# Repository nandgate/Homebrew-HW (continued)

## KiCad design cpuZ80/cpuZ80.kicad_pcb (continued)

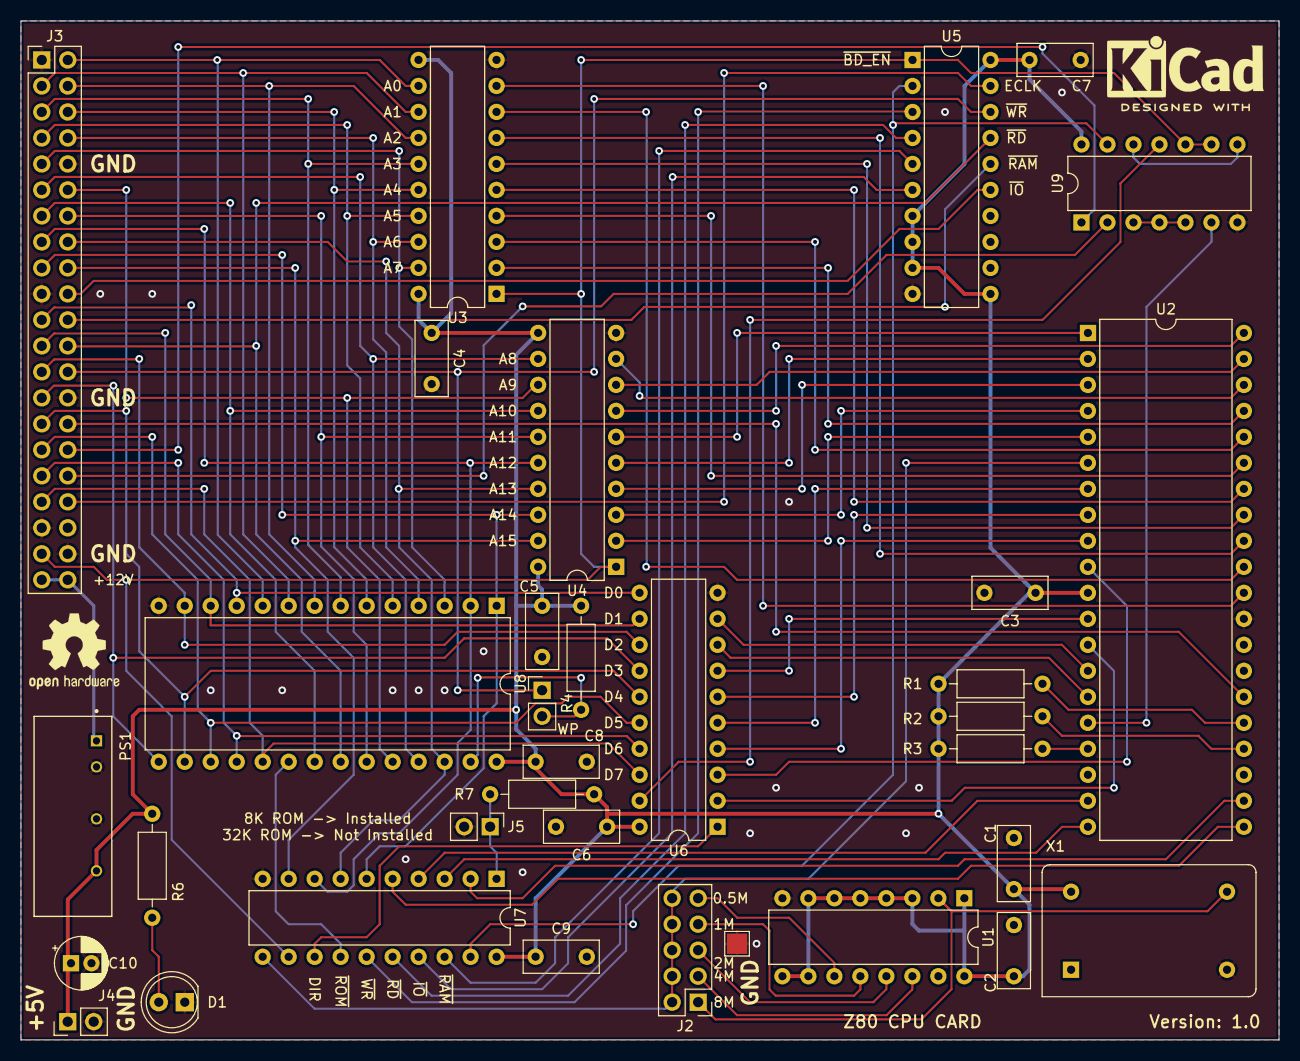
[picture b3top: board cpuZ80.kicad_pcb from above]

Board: 2 copper layers, 122.9 x 99.6 mm, 34 parts (0 on the bottom side), 87 nets.

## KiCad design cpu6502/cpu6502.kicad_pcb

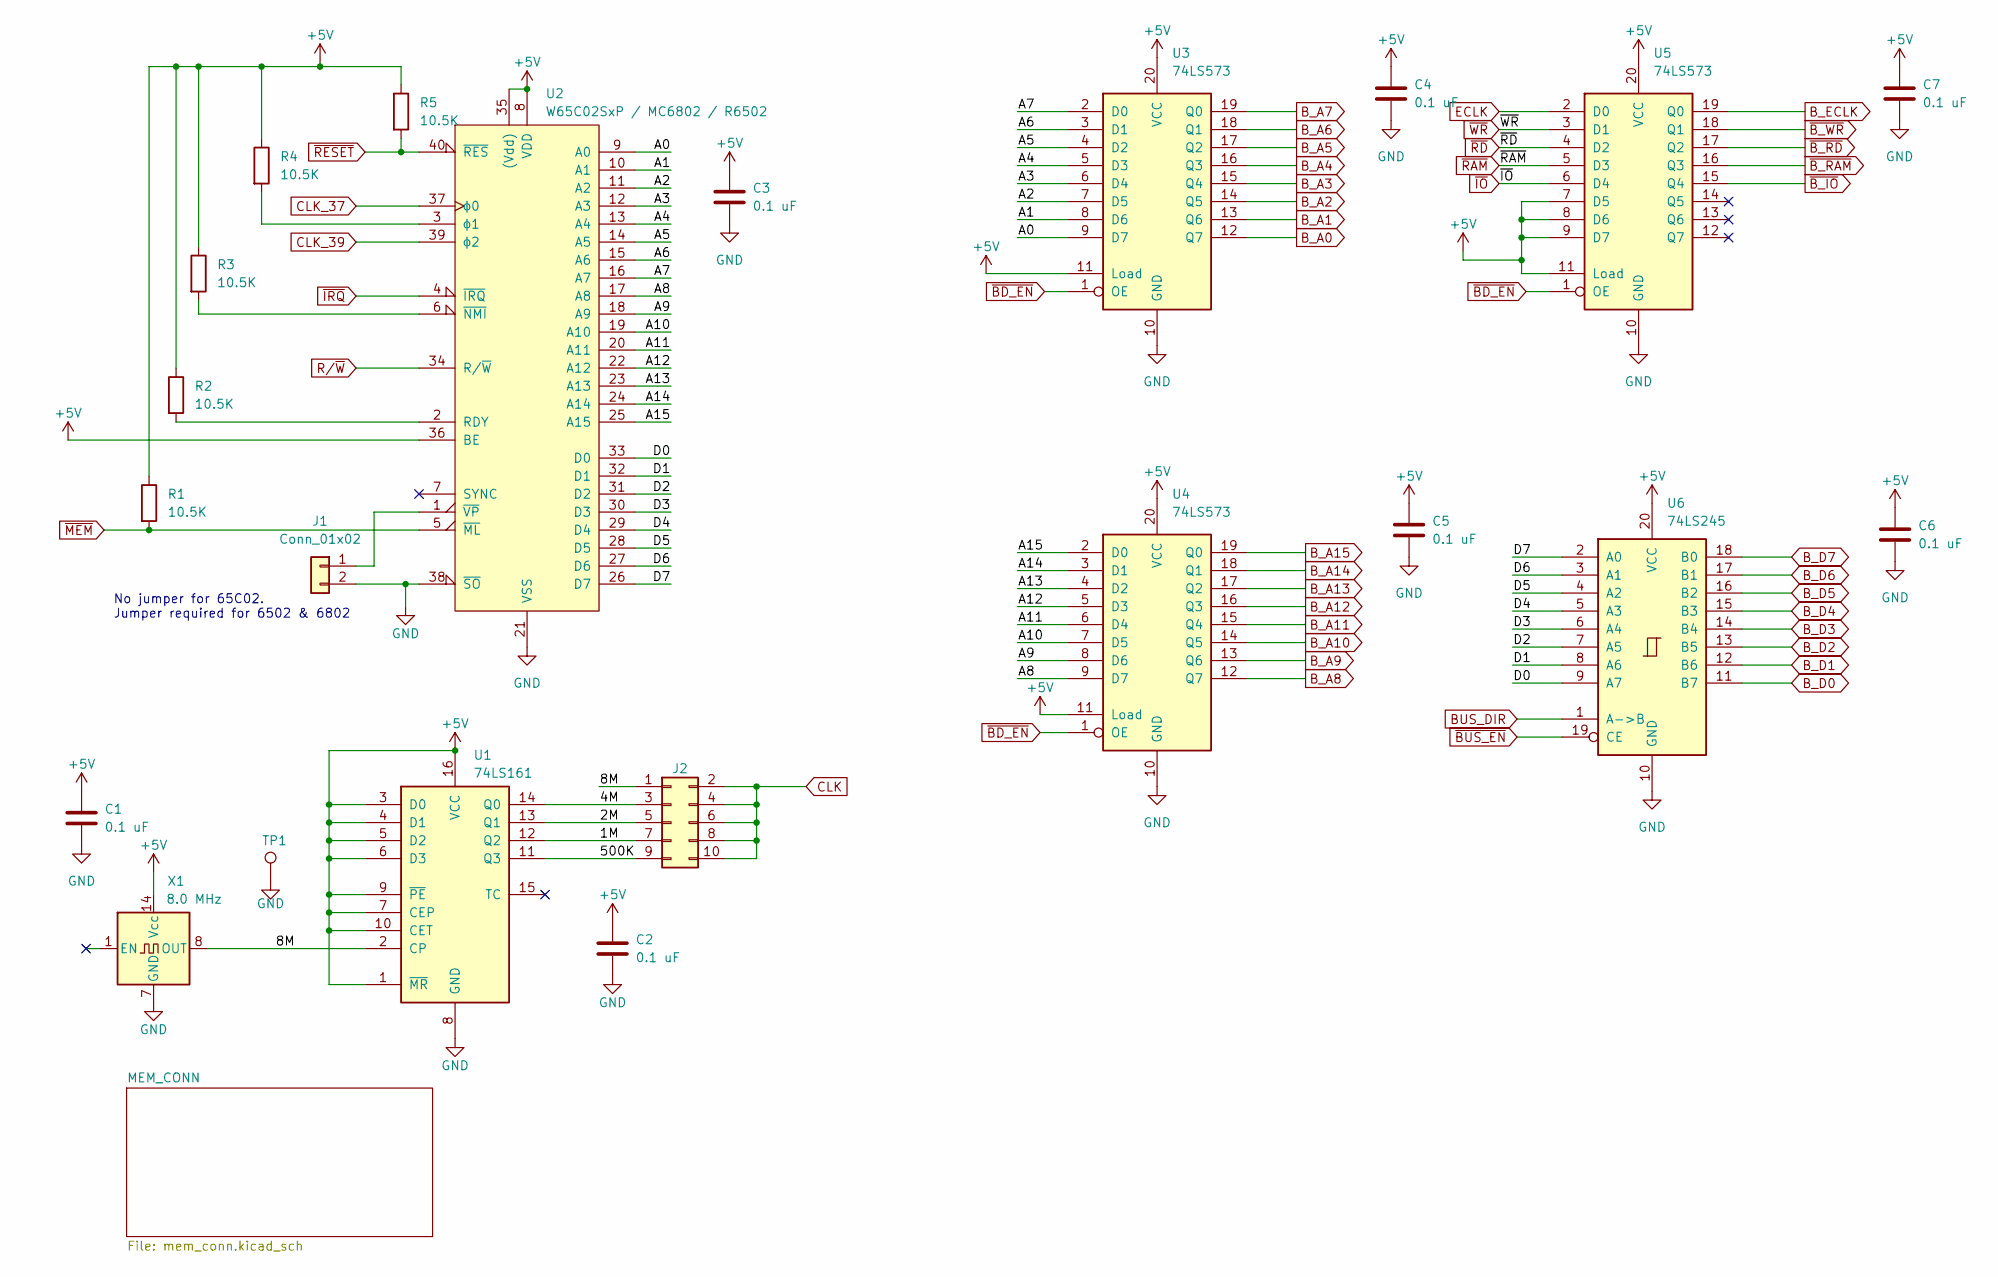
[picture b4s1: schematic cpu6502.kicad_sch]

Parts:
C1, C2, C3, C4, C5, C6, C7: 0.1 uF; C_Rect_L7.2mm_W3.0mm_P5.00mm_FKS2_FKP2_MKS2_MKP2
J1: Conn_01x02; PinHeader_1x02_P2.54mm_Vertical
J2: Conn_02x05_Odd_Even; PinHeader_2x05_P2.54mm_Vertical
R1, R2, R3, R4, R5: 10.5K; R_Axial_DIN0207_L6.3mm_D2.5mm_P10.16mm_Horizontal
TP1: TestPoint; TestPoint_Pad_2.0x2.0mm
U1: 74LS161; DIP-16_W7.62mm
U2: W65C02SxP / MC6802 / R6502; DIP-40_W15.24mm
U3, U4, U5: 74LS573; DIP-20_W7.62mm
U6: 74LS245; DIP-20_W7.62mm
X1: 8.0 MHz; Oscillator_DIP-14

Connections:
+5V: C1.1, C2.1, C3.1, C4.1, C5.1, C6.1, C7.1, R1.1, R2.1, R3.1, R4.1, R5.1, U1.1 (~MR), U1.3 (D0), U1.4 (D1), U1.5 (D2), U1.6 (D3), U1.7 (CEP), U1.9 (~PE), U1.10 (CET), U1.16 (VCC), U2.8 (VDD), U2.35 ((Vdd)), U2.36 (BE), U3.11 (Load), U3.20 (VCC), U4.11 (Load), U4.20 (VCC), U5.7 (D5), U5.8 (D6), U5.9 (D7), U5.11 (Load), U5.20 (VCC), U6.20 (VCC), X1.14 (Vcc); also elsewhere on the board
/1M: J2.7, U1.12 (Q2)
/2M: J2.5, U1.13 (Q1)
/4M: J2.3, U1.14 (Q0)
/8M: J2.1, U1.2 (CP), X1.8 (OUT)
/500K: J2.9, U1.11 (Q3)
/A0: U2.9 (A0), U3.9 (D7)
/A1: U2.10 (A1), U3.8 (D6)
/A2: U2.11 (A2), U3.7 (D5)
/A3: U2.12 (A3), U3.6 (D4)
/A4: U2.13 (A4), U3.5 (D3)
/A5: U2.14 (A5), U3.4 (D2)
/A6: U2.15 (A6), U3.3 (D1)
/A7: U2.16 (A7), U3.2 (D0)
/A8: U2.17 (A8), U4.9 (D7)
/A9: U2.18 (A9), U4.8 (D6)
/A10: U2.19 (A10), U4.7 (D5)
/A11: U2.20 (A11), U4.6 (D4)
/A12: U2.22 (A12), U4.5 (D3)
/A13: U2.23 (A13), U4.4 (D2)
/A14: U2.24 (A14), U4.3 (D1)
/A15: U2.25 (A15), U4.2 (D0)
/D0: U2.33 (D0), U6.9 (A7)
/D1: U2.32 (D1), U6.8 (A6)
/D2: U2.31 (D2), U6.7 (A5)
/D3: U2.30 (D3), U6.6 (A4)
/D4: U2.29 (D4), U6.5 (A3)
/D5: U2.28 (D5), U6.4 (A2)
/D6: U2.27 (D6), U6.3 (A1)
/D7: U2.26 (D7), U6.2 (A0)
BUS_DIR: U6.1 (A->B); also elsewhere on the board
B_A0: U3.12 (Q7); also elsewhere on the board
B_A1: U3.13 (Q6); also elsewhere on the board
B_A2: U3.14 (Q5); also elsewhere on the board
B_A3: U3.15 (Q4); also elsewhere on the board
B_A4: U3.16 (Q3); also elsewhere on the board
B_A5: U3.17 (Q2); also elsewhere on the board
B_A6: U3.18 (Q1); also elsewhere on the board
B_A7: U3.19 (Q0); also elsewhere on the board
B_A8: U4.12 (Q7); also elsewhere on the board
B_A9: U4.13 (Q6); also elsewhere on the board
B_A10: U4.14 (Q5); also elsewhere on the board
B_A11: U4.15 (Q4); also elsewhere on the board
B_A12: U4.16 (Q3); also elsewhere on the board
B_A13: U4.17 (Q2); also elsewhere on the board
B_A14: U4.18 (Q1); also elsewhere on the board
B_A15: U4.19 (Q0); also elsewhere on the board
B_D0: U6.11 (B7); also elsewhere on the board
B_D1: U6.12 (B6); also elsewhere on the board
B_D2: U6.13 (B5); also elsewhere on the board
B_D3: U6.14 (B4); also elsewhere on the board
B_D4: U6.15 (B3); also elsewhere on the board
B_D5: U6.16 (B2); also elsewhere on the board
B_D6: U6.17 (B1); also elsewhere on the board
B_D7: U6.18 (B0); also elsewhere on the board
B_ECLK: U5.19 (Q0); also elsewhere on the board
CLK: J2.2, J2.4, J2.6, J2.8, J2.10; also elsewhere on the board
CLK_37: U2.37 (ϕ0); also elsewhere on the board
CLK_39: U2.39 (ϕ2); also elsewhere on the board
ECLK: U5.2 (D0); also elsewhere on the board
GND: C1.2, C2.2, C3.2, C4.2, C5.2, C6.2, C7.2, J1.2, TP1.1, U1.8 (GND), U2.21 (VSS), U2.38 (~SO), U3.10 (GND), U4.10 (GND), U5.10 (GND), U6.10 (GND), X1.7 (GND); also elsewhere on the board
unnamed: J1.1, U2.1 (~VP)
unnamed: R2.2, U2.2 (RDY)
unnamed: R3.2, U2.6 (~NMI)
unnamed: R4.2, U2.3 (ϕ1)
R/~W: U2.34 (R/~W); also elsewhere on the board
~BD_EN: U3.1 (OE), U4.1 (OE), U5.1 (OE); also elsewhere on the board
~BUS_EN: U6.19 (CE); also elsewhere on the board
~B_IO: U5.15 (Q4); also elsewhere on the board
~B_RAM: U5.16 (Q3); also elsewhere on the board
~B_RD: U5.17 (Q2); also elsewhere on the board
~B_WR: U5.18 (Q1); also elsewhere on the board
~IO: U5.6 (D4); also elsewhere on the board
~IRQ: U2.4 (~IRQ); also elsewhere on the board
~MEM: R1.2, U2.5 (~ML); also elsewhere on the board
~RAM: U5.5 (D3); also elsewhere on the board
~RD: U5.4 (D2); also elsewhere on the board
~RESET: R5.2, U2.40 (~RES); also elsewhere on the board
~WR: U5.3 (D1); also elsewhere on the board

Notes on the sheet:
No jumper for 65C02. Jumper required for 6502 & 6802

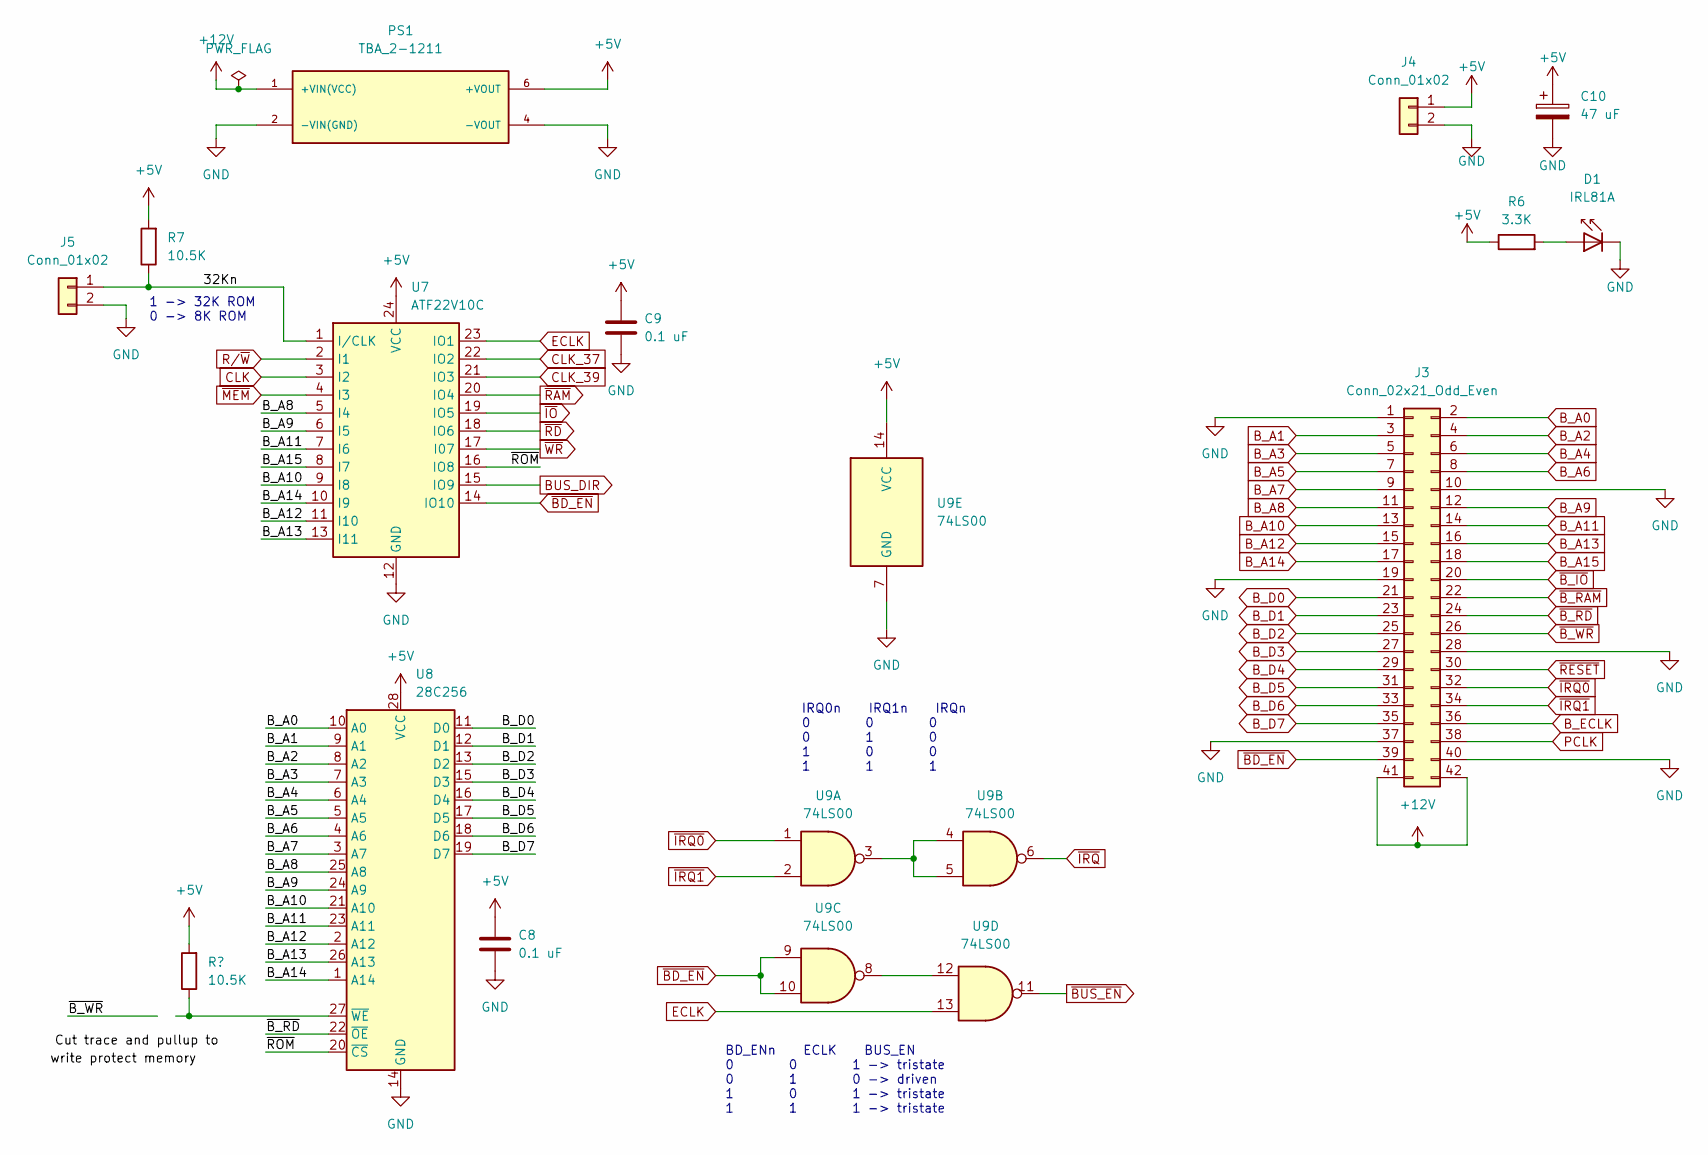
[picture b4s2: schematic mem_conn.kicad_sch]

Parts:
C8, C9: 0.1 uF; C_Rect_L7.2mm_W3.0mm_P5.00mm_FKS2_FKP2_MKS2_MKP2
C10: 47 uF; CP_Radial_D5.0mm_P2.00mm
D1: IRL81A; LED_D5.0mm
J3: Conn_02x21_Odd_Even; PinHeader_2x21_P2.54mm_Vertical
J4, J5: Conn_01x02; PinHeader_1x02_P2.54mm_Vertical
PS1: TBA_2-1211; CONV_TBA_2-1211; PARTREV April 19, 2021
R6: 3.3K; R_Axial_DIN0207_L6.3mm_D2.5mm_P10.16mm_Horizontal
R7: 10.5K; R_Axial_DIN0207_L6.3mm_D2.5mm_P10.16mm_Horizontal
U7: ATF22V10C; DIP-24_W7.62mm
U8: 28C256; DIP-28_W15.24mm
U9: 74LS00; DIP-14_W7.62mm

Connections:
+5V: C8.1, C9.1, C10.1, J4.1, PS1.6 (+VOUT), R6.1, R7.2, U7.24 (VCC), U8.28 (VCC), U9.14 (VCC); also elsewhere on the board
+12V: J3.41, J3.42, PS1.1 (+VIN(VCC))
/MEM_CONN/32Kn: J5.1, R7.1, U7.1 (I/CLK)
/MEM_CONN/~ROM: U7.16 (IO8), U8.20 (~CS)
BUS_DIR: U7.15 (IO9); also elsewhere on the board
B_A0: J3.2, U8.10 (A0); also elsewhere on the board
B_A1: J3.3, U8.9 (A1); also elsewhere on the board
B_A2: J3.4, U8.8 (A2); also elsewhere on the board
B_A3: J3.5, U8.7 (A3); also elsewhere on the board
B_A4: J3.6, U8.6 (A4); also elsewhere on the board
B_A5: J3.7, U8.5 (A5); also elsewhere on the board
B_A6: J3.8, U8.4 (A6); also elsewhere on the board
B_A7: J3.9, U8.3 (A7); also elsewhere on the board
B_A8: J3.11, U7.5 (I4), U8.25 (A8); also elsewhere on the board
B_A9: J3.12, U7.6 (I5), U8.24 (A9); also elsewhere on the board
B_A10: J3.13, U7.9 (I8), U8.21 (A10); also elsewhere on the board
B_A11: J3.14, U7.7 (I6), U8.23 (A11); also elsewhere on the board
B_A12: J3.15, U7.11 (I10), U8.2 (A12); also elsewhere on the board
B_A13: J3.16, U7.13 (I11), U8.26 (A13); also elsewhere on the board
B_A14: J3.17, U7.10 (I9), U8.1 (A14); also elsewhere on the board
B_A15: J3.18, U7.8 (I7); also elsewhere on the board
B_D0: J3.21, U8.11 (D0); also elsewhere on the board
B_D1: J3.23, U8.12 (D1); also elsewhere on the board
B_D2: J3.25, U8.13 (D2); also elsewhere on the board
B_D3: J3.27, U8.15 (D3); also elsewhere on the board
B_D4: J3.29, U8.16 (D4); also elsewhere on the board
B_D5: J3.31, U8.17 (D5); also elsewhere on the board
B_D6: J3.33, U8.18 (D6); also elsewhere on the board
B_D7: J3.35, U8.19 (D7); also elsewhere on the board
B_ECLK: J3.36; also elsewhere on the board
CLK: U7.3 (I2); also elsewhere on the board
CLK_37: U7.22 (IO2); also elsewhere on the board
CLK_39: U7.21 (IO3); also elsewhere on the board
ECLK: U7.23 (IO1), U9.13; also elsewhere on the board
GND: C8.2, C9.2, C10.2, D1.1 (K), J3.1, J3.10, J3.19, J3.28, J3.37, J3.40, J4.2, J5.2, PS1.2 (-VIN(GND)), PS1.4 (-VOUT), U7.12 (GND), U8.14 (GND), U9.7 (GND); also elsewhere on the board
unnamed: D1.2 (A), R6.2
unnamed: U9.3, U9.4, U9.5
unnamed: U9.8, U9.12
PCLK: J3.38
R/~W: U7.2 (I1); also elsewhere on the board
~BD_EN: J3.39, U7.14 (IO10), U9.9, U9.10; also elsewhere on the board
~BUS_EN: U9.11; also elsewhere on the board
~B_IO: J3.20; also elsewhere on the board
~B_RAM: J3.22; also elsewhere on the board
~B_RD: J3.24, U8.22 (~OE); also elsewhere on the board
~B_WR: J3.26, U8.27 (~WE); also elsewhere on the board
~IO: U7.19 (IO5); also elsewhere on the board
~IRQ0: J3.32, U9.1
~IRQ1: J3.34, U9.2
~IRQ: U9.6; also elsewhere on the board
~MEM: U7.4 (I3); also elsewhere on the board
~RAM: U7.20 (IO4); also elsewhere on the board
~RD: U7.18 (IO6); also elsewhere on the board
~RESET: J3.30; also elsewhere on the board
~WR: U7.17 (I07); also elsewhere on the board

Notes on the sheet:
1 -> 32K ROM 0 -> 8K ROM
IRQ0n IRQ1n IRQn 0 0 0 0 1 0 1 0 0 1 1 1
BD_ENn ECLK BUS_EN 0 0 1 -> tristate 0 1 0 -> driven 1 0 1 -> tristate 1 1 1 -> tristate

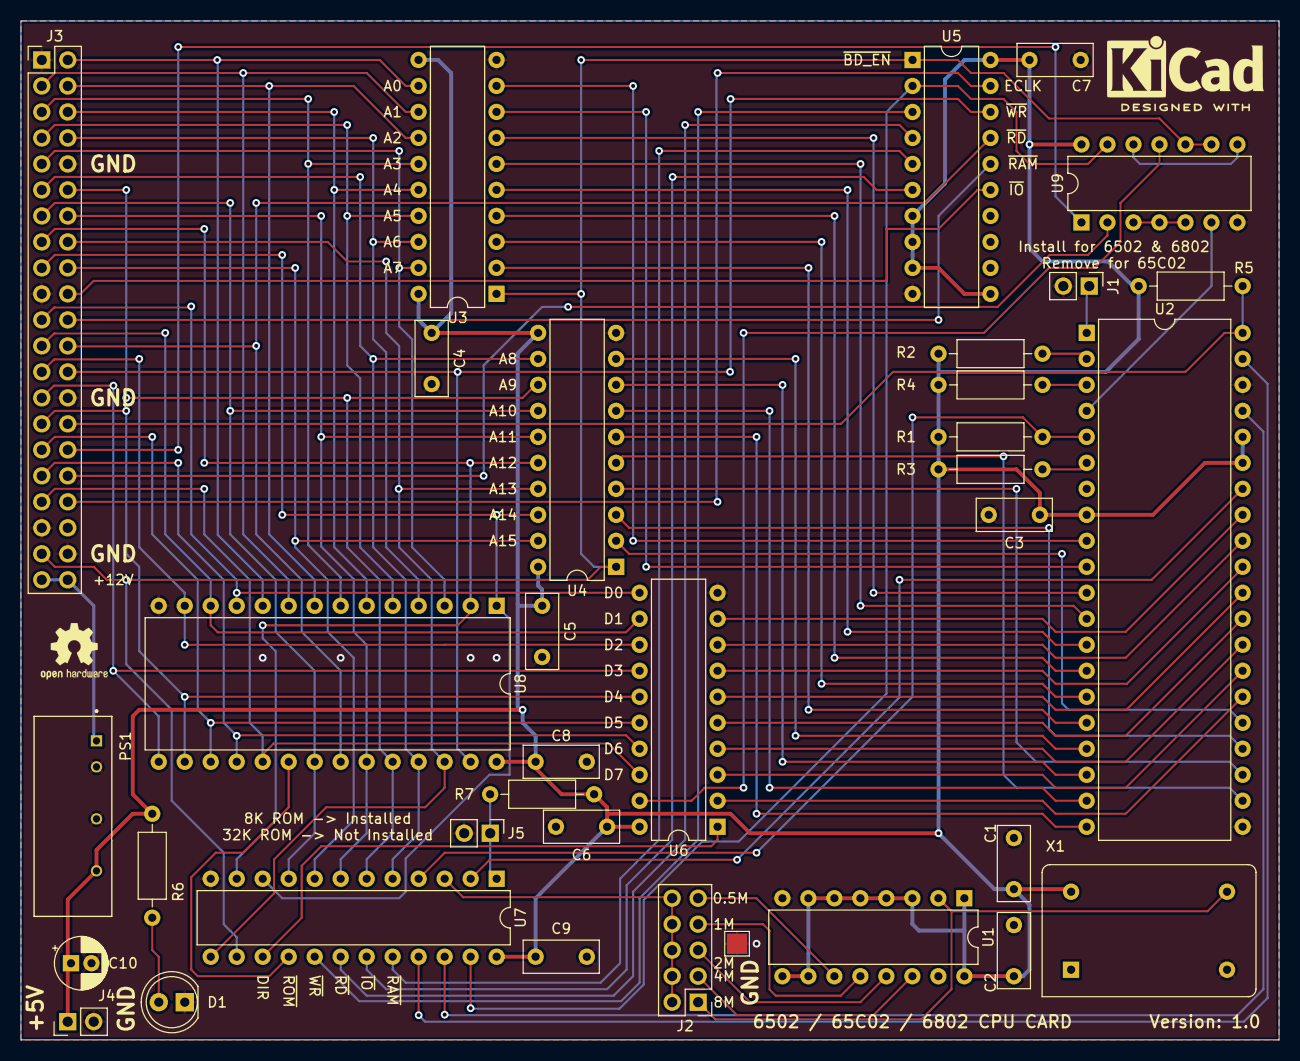
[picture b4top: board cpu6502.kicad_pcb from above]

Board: 2 copper layers, 122.9 x 99.6 mm, 35 parts (0 on the bottom side), 87 nets.

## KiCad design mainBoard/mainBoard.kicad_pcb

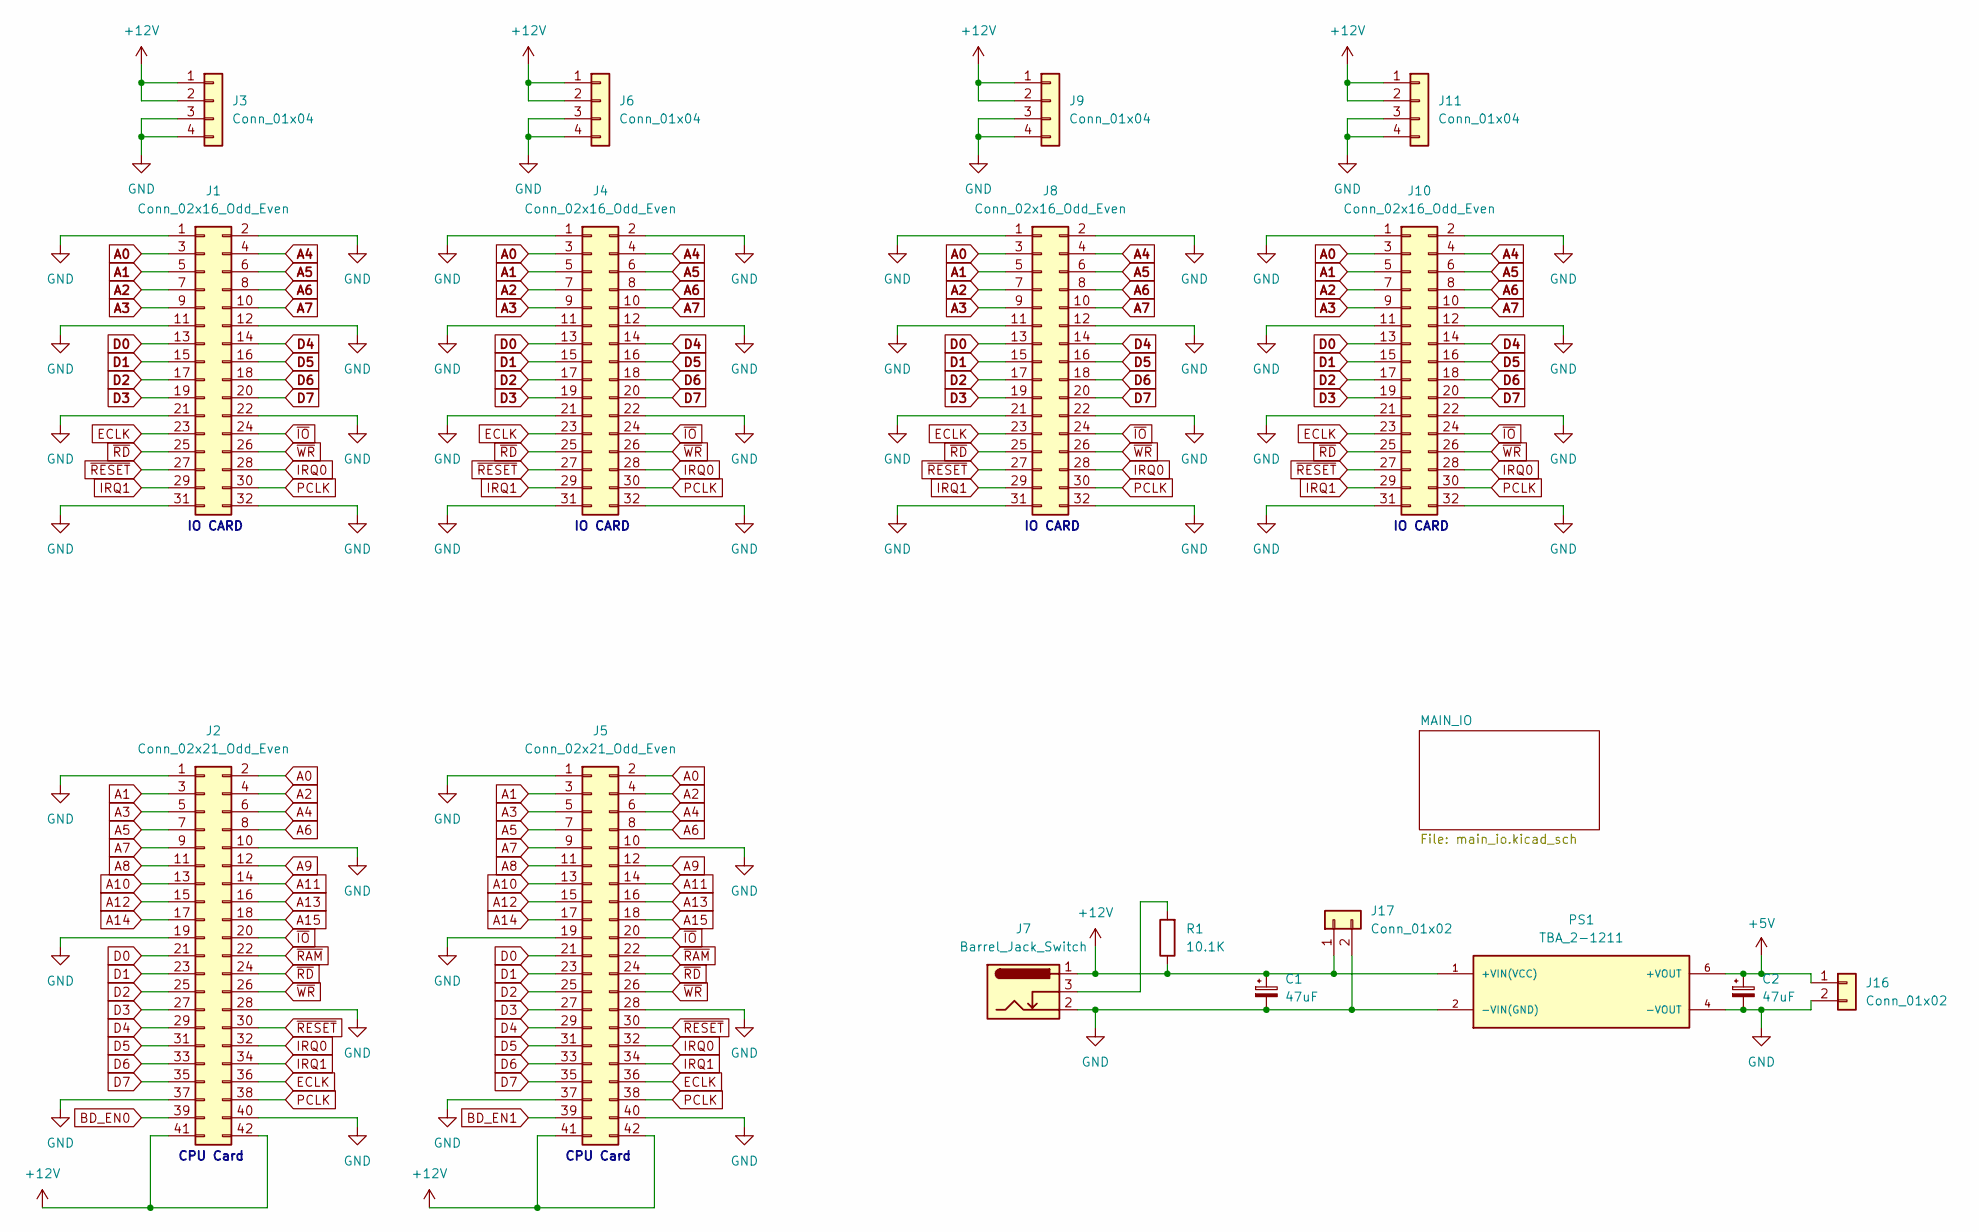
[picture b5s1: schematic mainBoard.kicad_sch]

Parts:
C1, C2: 47uF; CP_Radial_D5.0mm_P2.00mm
J1, J4, J8, J10: Conn_02x16_Odd_Even; PinSocket_2x16_P2.54mm_Vertical
J2, J5: Conn_02x21_Odd_Even; PinSocket_2x21_P2.54mm_Vertical
J3, J6, J9, J11: Conn_01x04; PinSocket_1x04_P2.54mm_Vertical
J7: Barrel_Jack_Switch; BarrelJack_Wuerth_6941xx301002
J16, J17: Conn_01x02; PinHeader_1x02_P2.54mm_Vertical
PS1: TBA_2-1211; CONV_TBA_2-1211; PARTREV April 19, 2021
R1: 10.1K; R_Axial_DIN0207_L6.3mm_D2.5mm_P10.16mm_Horizontal

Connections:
+5V: C2.1, J16.1, PS1.6 (+VOUT); also elsewhere on the board
+12V: C1.1, J2.41, J2.42, J3.1, J3.2, J5.41, J5.42, J6.1, J6.2, J7.1, J9.1, J9.2, J11.1, J11.2, J17.1, PS1.1 (+VIN(VCC)), R1.1
A0: J1.3, J2.2, J4.3, J5.2, J8.3, J10.3; also elsewhere on the board
A1: J1.5, J2.3, J4.5, J5.3, J8.5, J10.5; also elsewhere on the board
A2: J1.7, J2.4, J4.7, J5.4, J8.7, J10.7; also elsewhere on the board
A3: J1.9, J2.5, J4.9, J5.5, J8.9, J10.9; also elsewhere on the board
A4: J1.4, J2.6, J4.4, J5.6, J8.4, J10.4; also elsewhere on the board
A5: J1.6, J2.7, J4.6, J5.7, J8.6, J10.6; also elsewhere on the board
A6: J1.8, J2.8, J4.8, J5.8, J8.8, J10.8; also elsewhere on the board
A7: J1.10, J2.9, J4.10, J5.9, J8.10, J10.10; also elsewhere on the board
A8: J2.11, J5.11; also elsewhere on the board
A9: J2.12, J5.12; also elsewhere on the board
A10: J2.13, J5.13; also elsewhere on the board
A11: J2.14, J5.14; also elsewhere on the board
A12: J2.15, J5.15; also elsewhere on the board
A13: J2.16, J5.16; also elsewhere on the board
A14: J2.17, J5.17; also elsewhere on the board
A15: J2.18, J5.18; also elsewhere on the board
BD_EN0: J2.39; also elsewhere on the board
BD_EN1: J5.39; also elsewhere on the board
D0: J1.13, J2.21, J4.13, J5.21, J8.13, J10.13; also elsewhere on the board
D1: J1.15, J2.23, J4.15, J5.23, J8.15, J10.15; also elsewhere on the board
D2: J1.17, J2.25, J4.17, J5.25, J8.17, J10.17; also elsewhere on the board
D3: J1.19, J2.27, J4.19, J5.27, J8.19, J10.19; also elsewhere on the board
D4: J1.14, J2.29, J4.14, J5.29, J8.14, J10.14; also elsewhere on the board
D5: J1.16, J2.31, J4.16, J5.31, J8.16, J10.16; also elsewhere on the board
D6: J1.18, J2.33, J4.18, J5.33, J8.18, J10.18; also elsewhere on the board
D7: J1.20, J2.35, J4.20, J5.35, J8.20, J10.20; also elsewhere on the board
ECLK: J1.23, J2.36, J4.23, J5.36, J8.23, J10.23; also elsewhere on the board
GND: C1.2, C2.2, J1.1, J1.2, J1.11, J1.12, J1.21, J1.22, J1.31, J1.32, J2.1, J2.10, J2.19, J2.28, J2.37, J2.40, J3.3, J3.4, J4.1, J4.2, J4.11, J4.12, J4.21, J4.22, J4.31, J4.32, J5.1, J5.10, J5.19, J5.28, J5.37, J5.40, J6.3, J6.4, J7.2, J8.1, J8.2, J8.11, J8.12, J8.21, J8.22, J8.31, J8.32, J9.3, J9.4, J10.1, J10.2, J10.11, J10.12, J10.21, J10.22, J10.31, J10.32, J11.3, J11.4, J16.2, J17.2, PS1.2 (-VIN(GND)), PS1.4 (-VOUT); also elsewhere on the board
IRQ0: J1.28, J2.32, J4.28, J5.32, J8.28, J10.28; also elsewhere on the board
IRQ1: J1.29, J2.34, J4.29, J5.34, J8.29, J10.29; also elsewhere on the board
unnamed: J7.3, R1.2
PCLK: J1.30, J2.38, J4.30, J5.38, J8.30, J10.30
~IO: J1.24, J2.20, J4.24, J5.20, J8.24, J10.24; also elsewhere on the board
~RAM: J2.22, J5.22; also elsewhere on the board
~RD: J1.25, J2.24, J4.25, J5.24, J8.25, J10.25; also elsewhere on the board
~RESET: J1.27, J2.30, J4.27, J5.30, J8.27, J10.27; also elsewhere on the board
~WR: J1.26, J2.26, J4.26, J5.26, J8.26, J10.26; also elsewhere on the board

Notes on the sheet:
CPU Card
IO CARD

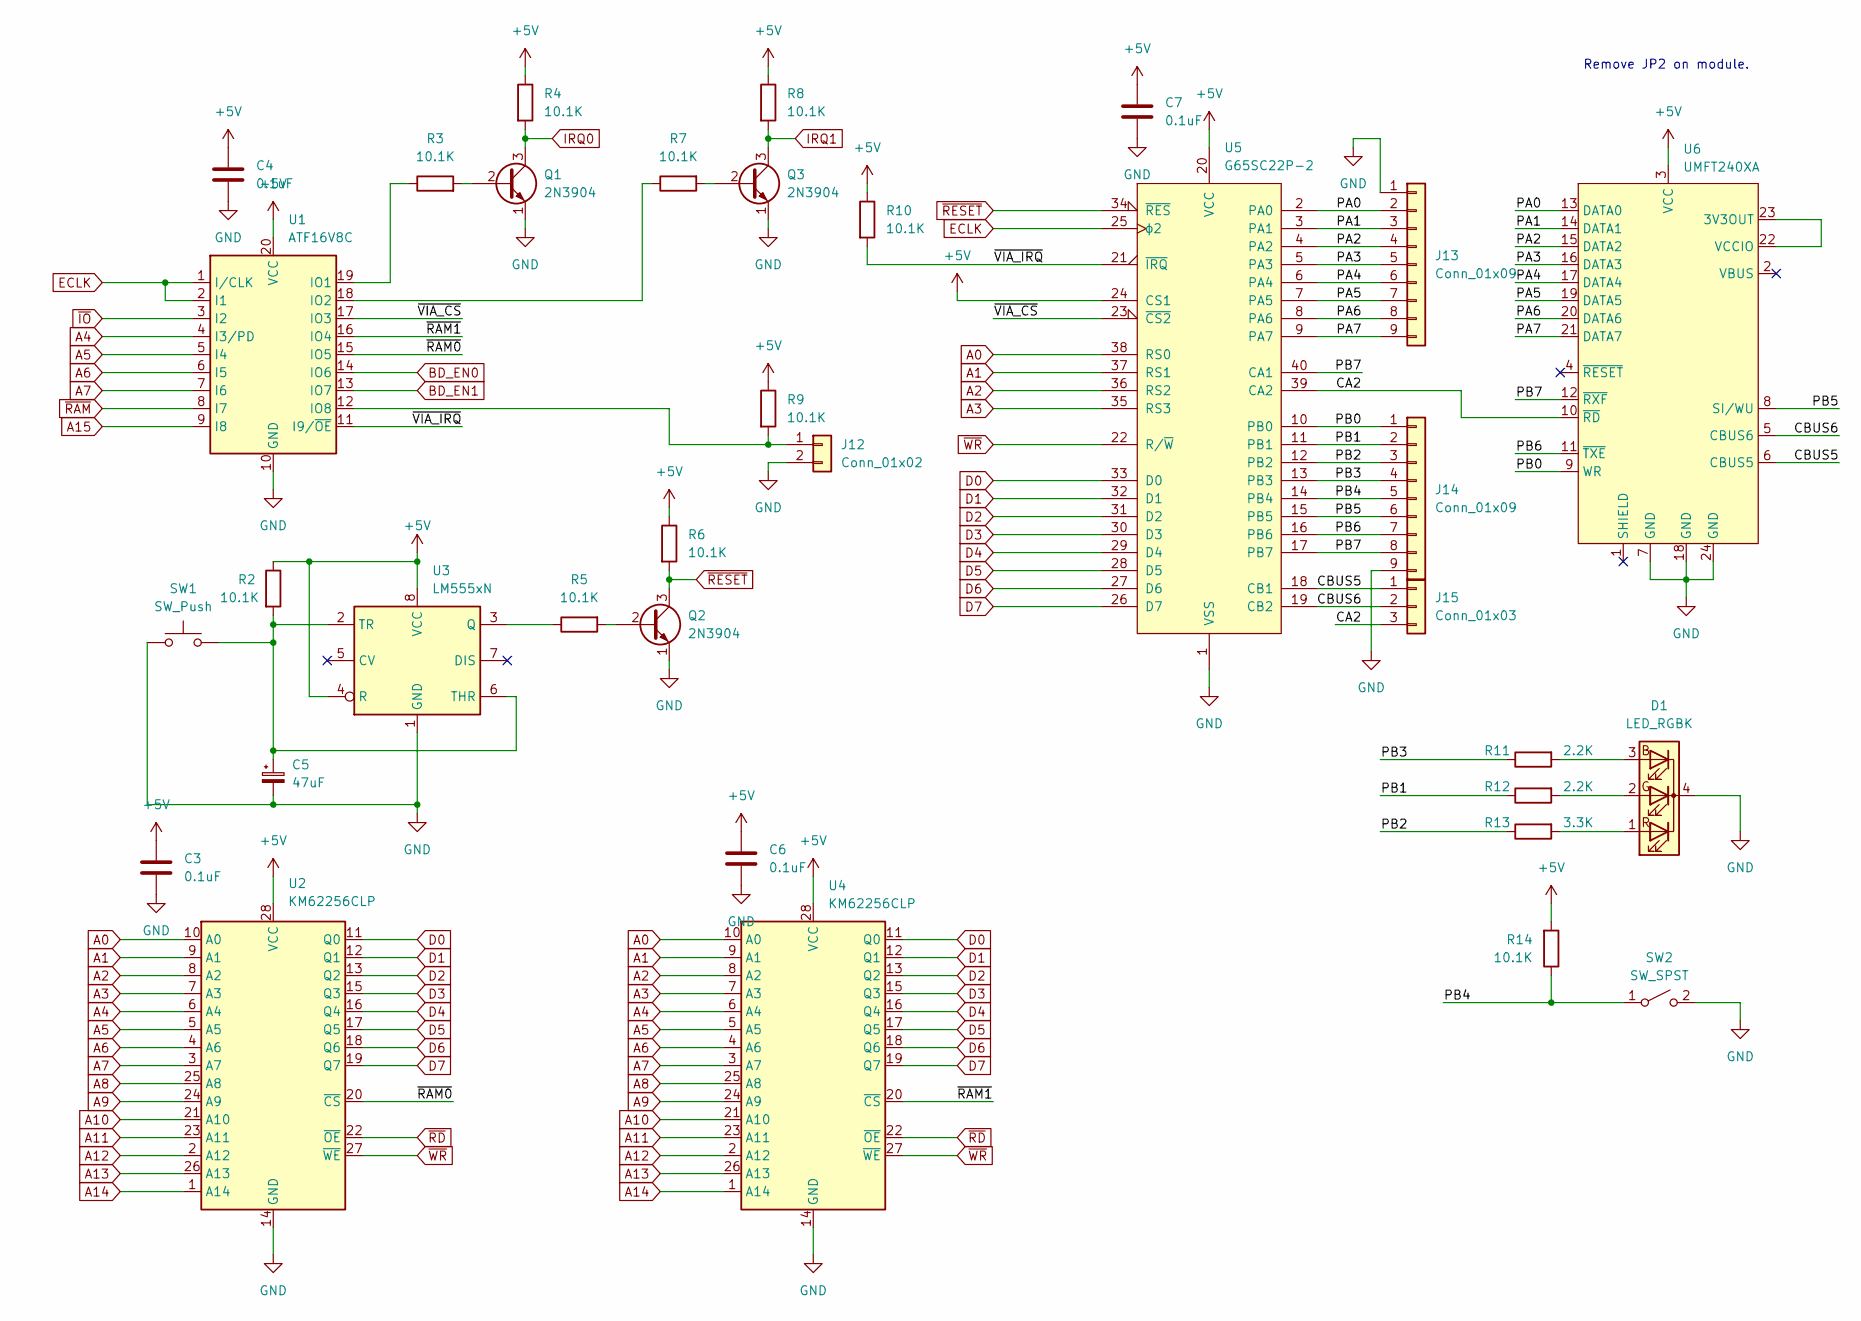
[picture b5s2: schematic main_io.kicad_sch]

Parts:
C3, C4, C6, C7: 0.1uF; C_Rect_L7.0mm_W2.5mm_P5.00mm
C5: 47uF; CP_Radial_D5.0mm_P2.00mm
D1: LED_RGBK; RGB_SMD_W7.8_H7.9
J12: Conn_01x02; PinHeader_1x02_P2.54mm_Vertical
J13, J14: Conn_01x09; PinHeader_1x09_P2.54mm_Vertical
J15: Conn_01x03; PinHeader_1x03_P2.54mm_Vertical
Q1, Q2, Q3: 2N3904; TO-92_Inline
R2, R3, R4, R5, R6, R7, R8, R9, R10, R14: 10.1K; R_Axial_DIN0207_L6.3mm_D2.5mm_P10.16mm_Horizontal
R11, R12: 2.2K; R_Axial_DIN0207_L6.3mm_D2.5mm_P10.16mm_Horizontal
R13: 3.3K; R_Axial_DIN0207_L6.3mm_D2.5mm_P10.16mm_Horizontal
SW1: SW_Push; SW_PUSH_6mm
SW2: SW_SPST; SW_DIP_SPSTx01_Slide_9.78x4.72mm_W7.62mm_P2.54mm
U1: ATF16V8C; DIP-20_W7.62mm_Socket_LongPads
U2, U4: KM62256CLP; DIP-28_W7.62mm_W15.64mm_LongPads
U3: LM555xN; DIP-8_W7.62mm
U5: G65SC22P-2; DIP-40_W15.24mm_Socket_LongPads
U6: UMFT240XA; DIP-24_W7.62mm_Socket_LongPads

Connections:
+5V: C3.1, C4.1, C6.1, C7.1, R2.1, R4.1, R6.1, R8.1, R9.1, R10.1, R14.2, U1.20 (VCC), U2.28 (VCC), U3.4 (R), U3.8 (VCC), U4.28 (VCC), U5.20 (VCC), U5.24 (CS1), U6.3 (VCC); also elsewhere on the board
/MAIN_IO/CA2: J15.3, U5.39 (CA2), U6.10 (~RD)
/MAIN_IO/CBUS5: J15.1, U5.18 (CB1), U6.6 (CBUS5)
/MAIN_IO/CBUS6: J15.2, U5.19 (CB2), U6.5 (CBUS6)
/MAIN_IO/PA0: J13.2, U5.2 (PA0), U6.13 (DATA0)
/MAIN_IO/PA1: J13.3, U5.3 (PA1), U6.14 (DATA1)
/MAIN_IO/PA2: J13.4, U5.4 (PA2), U6.15 (DATA2)
/MAIN_IO/PA3: J13.5, U5.5 (PA3), U6.16 (DATA3)
/MAIN_IO/PA4: J13.6, U5.6 (PA4), U6.17 (DATA4)
/MAIN_IO/PA5: J13.7, U5.7 (PA5), U6.19 (DATA5)
/MAIN_IO/PA6: J13.8, U5.8 (PA6), U6.20 (DATA6)
/MAIN_IO/PA7: J13.9, U5.9 (PA7), U6.21 (DATA7)
/MAIN_IO/PB0: J14.1, U5.10 (PB0), U6.9 (WR)
/MAIN_IO/PB1: J14.2, R12.1, U5.11 (PB1)
/MAIN_IO/PB2: J14.3, R13.1, U5.12 (PB2)
/MAIN_IO/PB3: J14.4, R11.1, U5.13 (PB3)
/MAIN_IO/PB4: J14.5, R14.1, SW2.1 (A), U5.14 (PB4)
/MAIN_IO/PB5: J14.6, U5.15 (PB5), U6.8 (SI/WU)
/MAIN_IO/PB6: J14.7, U5.16 (PB6), U6.11 (~TXE)
/MAIN_IO/PB7: J14.8, U5.17 (PB7), U5.40 (CA1), U6.12 (~RXF)
/MAIN_IO/~RAM0: U1.15 (IO5), U2.20 (~CS)
/MAIN_IO/~RAM1: U1.16 (IO4), U4.20 (~CS)
/MAIN_IO/~VIA_CS: U1.17 (IO3), U5.23 (~CS2)
/MAIN_IO/~VIA_IRQ: R10.2, U1.11 (I9/~OE), U5.21 (~IRQ)
A0: U2.10 (A0), U4.10 (A0), U5.38 (RS0); also elsewhere on the board
A1: U2.9 (A1), U4.9 (A1), U5.37 (RS1); also elsewhere on the board
A2: U2.8 (A2), U4.8 (A2), U5.36 (RS2); also elsewhere on the board
A3: U2.7 (A3), U4.7 (A3), U5.35 (RS3); also elsewhere on the board
A4: U1.4 (I3/PD), U2.6 (A4), U4.6 (A4); also elsewhere on the board
A5: U1.5 (I4), U2.5 (A5), U4.5 (A5); also elsewhere on the board
A6: U1.6 (I5), U2.4 (A6), U4.4 (A6); also elsewhere on the board
A7: U1.7 (I6), U2.3 (A7), U4.3 (A7); also elsewhere on the board
A8: U2.25 (A8), U4.25 (A8); also elsewhere on the board
A9: U2.24 (A9), U4.24 (A9); also elsewhere on the board
A10: U2.21 (A10), U4.21 (A10); also elsewhere on the board
A11: U2.23 (A11), U4.23 (A11); also elsewhere on the board
A12: U2.2 (A12), U4.2 (A12); also elsewhere on the board
A13: U2.26 (A13), U4.26 (A13); also elsewhere on the board
A14: U2.1 (A14), U4.1 (A14); also elsewhere on the board
A15: U1.9 (I8); also elsewhere on the board
BD_EN0: U1.14 (IO6); also elsewhere on the board
BD_EN1: U1.13 (IO7); also elsewhere on the board
D0: U2.11 (Q0), U4.11 (Q0), U5.33 (D0); also elsewhere on the board
D1: U2.12 (Q1), U4.12 (Q1), U5.32 (D1); also elsewhere on the board
D2: U2.13 (Q2), U4.13 (Q2), U5.31 (D2); also elsewhere on the board
D3: U2.15 (Q3), U4.15 (Q3), U5.30 (D3); also elsewhere on the board
D4: U2.16 (Q4), U4.16 (Q4), U5.29 (D4); also elsewhere on the board
D5: U2.17 (Q5), U4.17 (Q5), U5.28 (D5); also elsewhere on the board
D6: U2.18 (Q6), U4.18 (Q6), U5.27 (D6); also elsewhere on the board
D7: U2.19 (Q7), U4.19 (Q7), U5.26 (D7); also elsewhere on the board
ECLK: U1.1 (I/CLK), U1.2 (I1), U5.25 (ϕ2); also elsewhere on the board
GND: C3.2, C4.2, C5.2, C6.2, C7.2, D1.4 (K), J12.2, J13.1, J14.9, Q1.1 (E), Q2.1 (E), Q3.1 (E), SW1.1, SW2.2 (B), U1.10 (GND), U2.14 (GND), U3.1 (GND), U4.14 (GND), U5.1 (VSS), U6.7 (GND), U6.18 (GND), U6.24 (GND); also elsewhere on the board
IRQ0: Q1.3 (C), R4.2; also elsewhere on the board
IRQ1: Q3.3 (C), R8.2; also elsewhere on the board
unnamed: C5.1, R2.2, SW1.2, U3.2 (TR), U3.6 (THR)
unnamed: D1.1 (RA), R13.2
unnamed: D1.2 (GA), R12.2
unnamed: D1.3 (BA), R11.2
unnamed: J12.1, R9.2, U1.12 (IO8)
unnamed: Q1.2 (B), R3.2
unnamed: Q2.2 (B), R5.2
unnamed: Q3.2 (B), R7.2
unnamed: R3.1, U1.19 (IO1)
unnamed: R5.1, U3.3 (Q)
unnamed: R7.1, U1.18 (IO2)
unnamed: U6.22 (VCCIO), U6.23 (3V3OUT)
~IO: U1.3 (I2); also elsewhere on the board
~RAM: U1.8 (I7); also elsewhere on the board
~RD: U2.22 (~OE), U4.22 (~OE); also elsewhere on the board
~RESET: Q2.3 (C), R6.2, U5.34 (~RES); also elsewhere on the board
~WR: U2.27 (~WE), U4.27 (~WE), U5.22 (R/~W); also elsewhere on the board

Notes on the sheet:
Remove JP2 on module.

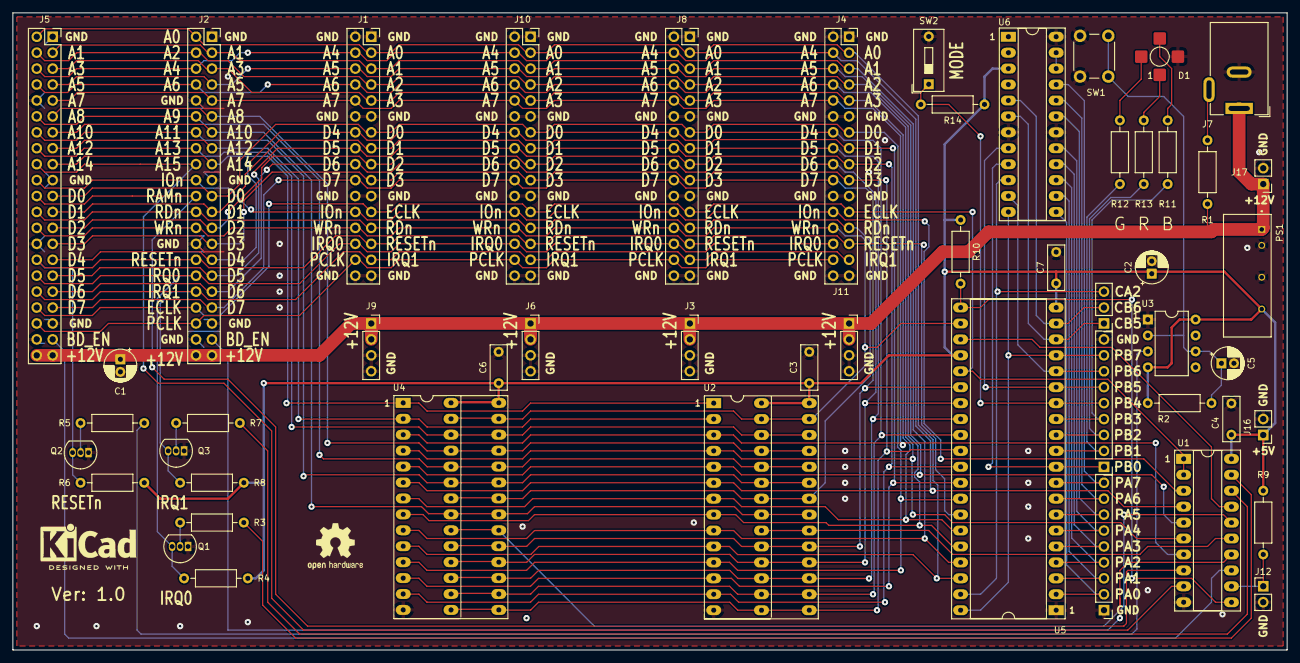
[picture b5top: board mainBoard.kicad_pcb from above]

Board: 2 copper layers, 203.2 x 101.6 mm, 51 parts (0 on the bottom side), 74 nets.
